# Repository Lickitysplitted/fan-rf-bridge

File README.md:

# Fan RF Bridge

Control RF-remote ceiling fans from Home Assistant, with two-way tracking: the
bridge transmits fan commands and also listens to the handheld remotes, so HA
stays in sync when someone uses the remote.

Hardware: a [wESP32](https://wesp32.com/) (PoE ESP32) running ESPHome, plus a
custom HAT carrying 433 MHz and 315 MHz ASK transmitters (NiceRF STX882) and
receivers (NiceRF SRX882S).

Fans are just what I built it for. The bridge can send and listen to most
fixed-code 433.92 MHz and 315 MHz OOK remotes: lights and plug-in outlets,
blinds and shades, fireplaces, doorbells, and wireless door/motion sensors
(receive only). The same capture → transmit script → template entity pattern
applies; see [Adding devices](#adding-devices). Rolling-code devices (garage
doors, car fobs, gates) and FSK remotes won't work.

> **This is a reference build, not a drop-in config.** Every remote ID and
> code in this repo belongs to my remotes, and the entity names match my
> five fans. Flashed as-is, it will control nothing of yours. Capture your own
> remotes and replace the codes first; see
> [Using it with your own fans](#using-it-with-your-own-fans) and
> [Adding devices](#adding-devices). Other fan models need their own decoding.

Supported fans (one transmitter per band drives every fan of that model; each
remote has its own ID):

| Model | Remote FCC ID | Band | Encoding | HA entities |
|---|---|---|---|---|
| A | 2ABUP-FT0317A | 433.92 MHz | 40-bit PWM: 24-bit remote ID + cmd byte ×2 | 6-speed fan + reverse button |
| B (Harbor Breeze) | A25-FA0188A | 315 MHz | Manchester OOK, replayed raw | 3-speed fan + light |

## Repo layout

| Path | What |
|---|---|
| `fan-control.yaml` | ESPHome config: TX scripts, RX decoders, fan/light entities |
| `fanb_codes.h` | Fan B raw pulse tables (TX) and the RX matcher |
| `secrets.example.yaml` | Template for `secrets.yaml` |
| `fanA-433.txt`, `fanA2-433.txt`, `fanB*-315.txt` | rtl_433 captures the codes were decoded from |
| `fanB_timings.json` | Fan B pulse trains extracted from the captures |
| `make_fana_iq.py`, `make_fanb_iq.py` | Generate HackRF IQ files to replay a command (used to verify codes before the hardware existed) |
| `fan A/B button presses.txt` | Order of button presses in the captures |
| `pcb/` | KiCad 10 project for the HAT, generated by `pcb/make_board.py`; Gerbers in `pcb/fan-hat-gerbers.zip`. See `pcb/README.md` |
| `case/` | 3D-printable case (tall base + magnetic lid). See `case/README.md` |

## Using it with your own fans

The remote IDs in `fan-control.yaml` and `fanb_codes.h` are for **my** remotes.
Even fans of the same models need changes: each remote has its own ID. Rename
or remove fan entities to match how many fans you have. To use your own:

1. Capture each remote (see [Capturing a remote](#capturing-a-remote)), or with an RTL-SDR and
   [rtl_433](https://github.com/merbanan/rtl_433) (`rtl_433 -f 433.92M -A` /
   `-f 315M -A`; 315 MHz needed low gain, `-g 9.9`).
2. Fan A: the 24-bit remote ID is the first 3 bytes of each frame; replace the
   `prefix:` strings and the `rid ==` checks in the RX lambda.
3. Fan B: replace the pulse tables in `fanb_codes.h` (decoded from the
   triq.org links rtl_433 prints).

Other remotes need their own decode, but the TX script / RX lambda / echo
suppression pattern carries over.

## Building the firmware

Replace the remote codes with your own first (see above). The capture step
below can run on the bridge before any codes are in.

```sh
pip install esphome
cp secrets.example.yaml secrets.yaml        # then fill in a key
esphome run fan-control.yaml                # first flash over USB/serial
esphome run fan-control.yaml --device <ip>  # later updates over the network
```

The wESP32's V+ defaults to 12 V; **bridge its 5 V jumper** before fitting the
radios.

## Adding devices

### Capturing a remote

The bridge can capture by itself. Temporarily add `dump:` to the receiver for
the band, flash, and watch the log while pressing each button a few times:

```yaml
remote_receiver:
  - id: rx433            # or rx315
    ...
    dump: all            # tries ESPHome's built-in decoders, then prints raw
```

```sh
esphome run fan-control.yaml --device fan-rf-bridge.local
esphome logs fan-control.yaml --device fan-rf-bridge.local > capture.txt
```

- If a built-in decoder (`rc_switch`, `nexa`, ...) recognises it, the log
  prints a ready-made transmit action. Use that and skip the raw tables.
- Otherwise you get `Received Raw:` lines: microsecond durations, positive =
  carrier on, negative = off. Each button repeats the same burst; diff the
  buttons to find the ID and command bits.
- The SRX882 stretches marks by up to ~150 µs on strong signals, so match on
  short/long rather than exact times (`fanb_match` does this).
- Remove `dump:` when done; it floods the log.

rtl_433 with an RTL-SDR does the same from a PC and auto-decodes many
protocols: `rtl_433 -f 433.92M -A` or `-f 315M -g 9.9 -A`. The original codes
in this repo came from those captures (`fanA-433.txt`, `fanB*-315.txt`).

Only 433.92 and 315 MHz OOK/ASK devices work with this hardware. FSK remotes,
other bands, and rolling-code devices (garage doors, cars) won't.

### Another fan of an existing model

**Model A** (needs its 24-bit remote ID, the first 3 bytes of a frame):

1. Copy the `Fan A1` block under `fan:`. Rename everything `a1` in it (`name`,
   `id`, the `&a1_speed` anchor and its `*a1_speed` alias, `id(fan_a1)` in the
   speed lambda), and put the new remote's ID as a 24-bit binary `prefix:` in
   both `script.execute` calls.
2. Copy a `Fan A1 Reverse` button with the same prefix.
3. In the `rx433` lambda, add the ID to the lookup:
   `rid == 0x00CE17 ? id(fan_a1) : rid == 0x114017 ? id(fan_a2) : rid == 0xNNNNNN ? id(fan_a3) : nullptr`.

**Model B** (replayed raw, so the pulse tables are needed):

1. In `fanb_codes.h`, grow `FANB[3][5]` to `FANB[4][5]` and add a row with the
   five raw trains (speed1, speed2, speed3, off, light), in that order.
   Different remote revisions use different command bytes (see the B3
   comment), so capture every button.
2. In `fanb_match` (same file), change `f < 3` to `f < 4`.
3. Copy the `Fan B3` block under `fan:`, rename `b3` → `b4` throughout
   (including `id(fan_b3)` in the speed lambda), and use `fan: 3` in its
   script calls.
4. Copy a Fan B light: the `out_light_b3` template output (with `fan: 3`)
   and its `light: binary` entry pointing at the new output.
5. In the `rx315` lambda, extend the two `fi == ...` chains to include the new
   fan and light.

### A different kind of device

Follow the same pattern as the fans:

1. **Capture and decode** (above). Note whether a command is absolute
   (e.g. "speed 2") or a toggle (e.g. "power"). Toggles can get out of step with
   HA, as with Fan A power.
2. **Transmit.** Add a script modelled on `fanb_send`. Use a built-in action
   if `dump: all` found one, otherwise `transmit_raw` with the timings.
   Real remotes repeat a frame 5–10 times, so do the same. Keep the script's
   two guards: skip sending while `from_rx` is set (so an RX state update
   doesn't retransmit) and set `last_tx` (so the bridge ignores hearing
   itself).
3. **Entities.** Pick a fitting `template` type (fan, light via a template
   output, switch, button) and call the script from its actions.
4. **Receive (optional).** Add a branch to the band's `on_raw` lambda that
   matches the frames, ignores repeats within 1 s, and publishes the new
   state with `from_rx` set.

Before the firmware existed, codes were first checked by replaying them with a
HackRF (`make_fana_iq.py` / `make_fanb_iq.py` → `hackrf_transfer -t`). You can
skip that step and test straight from the bridge.

## Operating it

**Adding to Home Assistant.** Plug the bridge into a PoE port. HA discovers it
under Settings → Devices & services as "Fan RF Bridge"; click Configure and
paste `api_encryption_key` from `secrets.yaml`. Give it a DHCP reservation so
OTA updates keep finding it (`fan-rf-bridge.local` also works).

**Entities.**

| Entity | What it does |
|---|---|
| Fan A1, Fan A2 | On/off and 6 speeds |
| Fan A1 Reverse, Fan A2 Reverse (buttons) | Flip the direction (summer/winter) |
| Fan B1, Fan B2, Fan B3 | On/off and 3 speeds |
| Fan B1 Light … Fan B3 Light | Fan light on/off |
| Status LED | The LED on the HAT (turn off if it bothers you) |

Use them like any HA fan or light: dashboard cards, voice assistants,
automations, scenes.

**Using the handheld remotes.** Keep using them. The bridge hears every press,
so HA updates to match within a second.

**State can drift.** The fans don't report back, so HA only knows what it
sent or heard. If a press is missed (remote out of range, bridge rebooting,
fan switched at the wall), HA shows the wrong state. To fix it, set the fan or
light in HA to what it really is, then press the button once more:

- Fan A power is a toggle. If HA says off while the fan is spinning, turn it
  "on" in HA (no change on the fan), then off.
- Fan B lights are a toggle too. Same fix: flip the HA light once to match,
  then use it normally.
- Fan B speeds and off are absolute, so they can't drift. Picking a speed
  always lands on that speed.

After a reboot or power loss everything shows off in HA, whatever the fans are
actually doing.

**Status LED.** Steady on = running normally. Slow blink = warning (e.g. HA not
connected yet). Fast blink = error.

**Updating firmware.** `esphome run fan-control.yaml --device fan-rf-bridge.local`.
It needs `ota_password` from `secrets.yaml`.

## Notes

- RF is one-way per command; fan state in HA is assumed, corrected by RX when a
  remote is used. Fan A power is a toggle code; Fan B light is a toggle.
- The bridge hears its own transmissions, so RX is ignored for 2 s after TX.
- Datasheets: wESP32 product brief (silicognition.com), NiceRF STX882 / SRX882
  (nicerf.com).

## License

MIT (see `LICENSE`), except `case/`, which is CC BY-NC-SA as a remix of
notjj's wESP32 case (see `case/README.md`).

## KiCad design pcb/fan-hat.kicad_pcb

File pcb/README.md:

# wESP32 RF hat (fan-hat)

75 × 40 mm board that stacks on top of the wESP32 on its four mounting holes and
plugs into JP1. Carries the two STX882 transmitters and two SRX882 receivers in
sockets, the 5 V → 3.3 V dividers for the receiver data lines, decoupling and a
status LED. Replaces the Perma-Proto + Adafruit 757.

Open `fan-hat.kicad_pro` in KiCad 10. `make_board.py` regenerates everything
(schematic, placed AND routed PCB with filled GND pours, custom footprint/symbol)
and checks that schematic nets == PCB pad nets, ERC and DRC (all clean):

    & "$env:LOCALAPPDATA\Programs\KiCad\10.0\bin\python.exe" make_board.py

Edit positions/nets/tracks in the script (`PARTS`, `TRACKS`), not in KiCad —
re-running overwrites the files. `fan-hat-gerbers.zip` is the fab upload
(2-layer, 1.6 mm, any finish; JLCPCB/PCBWay 5 pcs).

## Geometry (from the product brief)

- Holes ⌀3.2 at 3.5 mm from each edge (wESP32: ⌀3, same spots), M2.5 hardware.
- JP1 pin 1 = OUTER column (1.8 mm from the right edge), 5.0 mm up from the
  bottom-right (non-plated) hole, header centred on the 40 mm axis; pin 2
  inboard, pin 3 above pin 1. **Caliper-check on the real board:** pin 1 at
  1.8 mm from the right edge, 8.6 mm from the bottom edge.
- Left 22 mm of the underside is kept empty: RJ45 (15.2 mm tall) and 12 mm
  electrolytics are there. Right end underside is the 2×10.
- SRX882: pins 2 and 6 are both GND, pins 1 and 7 both ANT (NiceRF datasheet,
  RFLink wiring page), so the socket is a plain 1×4 on pins 3–6 (VCC, CS, DATA,
  GND). Pins 1–2 hang free above the board (measured pin 2 → 3 gap 18.22 mm is
  drawn on silk only). Coil solders to pin 1 or the pin-7 hole.
- Modules lie FLAT in their sockets (pins straight, not bent): the pin row is
  1.2 mm (SRX) / 1.8 mm (STX) from one long edge and the body lies over the
  board. The unit mounts on the wall with the RJ45 end DOWN, so "up" is the
  JP1 end (+x): the two SRX882 lie along the board with pin 1 (ANT end) toward
  +x, the two STX882 sit at the top with their bodies overhanging the JP1 pads
  (they are 8.5 mm up on their sockets — pads and screw heads are below them).
  All four ANT holes (silk circles) face +x, so the coils exit past the top edge.
  STX882 ANT pad is at the DATA end of the socket (confirmed from the module).

## Stack

Hat underside is 18 mm above the wESP32 top (M2.5 × 18 mm standoffs ×4).
JP1 ships as bare pads. Used: 3M 929836-04-10 2x10 header soldered into
JP1 UPSIDE DOWN (short 6 mm side in the board, 12.95 mm side pointing up; trim
the stubs underneath), mating a plain 2x10 female socket (8.5 mm body) on the
hat's underside. Socket opening sits ~9.5 mm above the wESP32, the pin tips at
~15.5 mm, so ~6 mm insertion. Ordinary 6 mm-pin headers won't reach.
Fallback: two Arduino-style stackable female headers plugged into each other
on JP1 and a plain male header on the hat - same footprint.

Above the hat: modules lie flat on 8.5 mm sockets, so ≈ 10–14 mm total; the
coil antennas solder to the ANT hole on each module and extend past the top
edge — the hat has no antenna pads.

## BOM

| Ref | Part | Qty |
|---|---|---|
| J1 | 2×10 female socket (hat) + 2×10 long-pin male header (wESP32 JP1) | 1 + 1 |
| U1, U2 | SRX882 (433, 315) on 1×4 female headers | 2 + 2 |
| U3, U4 | STX882 (433, 315) on 1×3 female header | 2 + 2 |
| R1, R3 | 10 kΩ axial | 2 |
| R2, R4 | 20 kΩ axial | 2 |
| R5 | 330 Ω axial | 1 |
| D1 | 3 mm LED | 1 |
| C1–C4 | 100 nF ceramic disc, 2.5 mm | 4 |
| C5 | 10 µF electrolytic, 5 mm ⌀, 2 mm pitch | 1 |
| H1–H4 | M2.5 × 18 mm standoff + screws | 4 |

Routing notes: JP1's odd column is reached through the 0.84 mm gap between the
header columns (IO23 on top, IO5 on the bottom), which boxes in pin 9 — so pin 9
is left NC and GND uses pins 1 and 19. GND is the pours on both sides plus two
short stitches (JP1.1→U4.3, D1.1→C5.2). No vias.

Nets: IO4 → STX-433 DATA, IO5 → STX-315 DATA, SRX-433 DATA → 10k/20k → IO34,
SRX-315 DATA → 10k/20k → IO35, IO23 → 330 Ω → LED. Everything runs on V+ (5 V,
jumper bridged); 3.3 V unused. Receiver CS tied to 5 V.

## Assembly note (case)

The printed case has magnet blocks in the corners at the antenna end that reach
up to 1 mm inside the HAT's long edges (x 69–75; the wESP32 sits 0.6 mm
off-centre in the case). Bend both SRX coils at least 2.5 mm inboard where they
pass that end: SRX-433 to y ≈ 5.5, SRX-315 to y ≈ 36.3. That clears the blocks
in either board orientation with ≥ 0.7 mm margin and passes over the STX
modules. The STX coils are already inboard.

Coil height: the case's antenna slot tops out 37 mm above the case floor, so
every coil must leave its module with its axis no more than 11 mm above the HAT
top. The module PCBs sit at 8.5–9.5 mm (socket + board), so solder each coil
with its lead bent so the coil runs level with the module board (axis ≈ 9.5–10
mm), not perched on top of it.

## Before ordering

1. Open the board in KiCad, run DRC once yourself, eyeball the 3D view.
2. Upload `fan-hat-gerbers.zip`.
3. Firmware already drives the LED (`status_led` light on GPIO23 in `fan-control.yaml`).

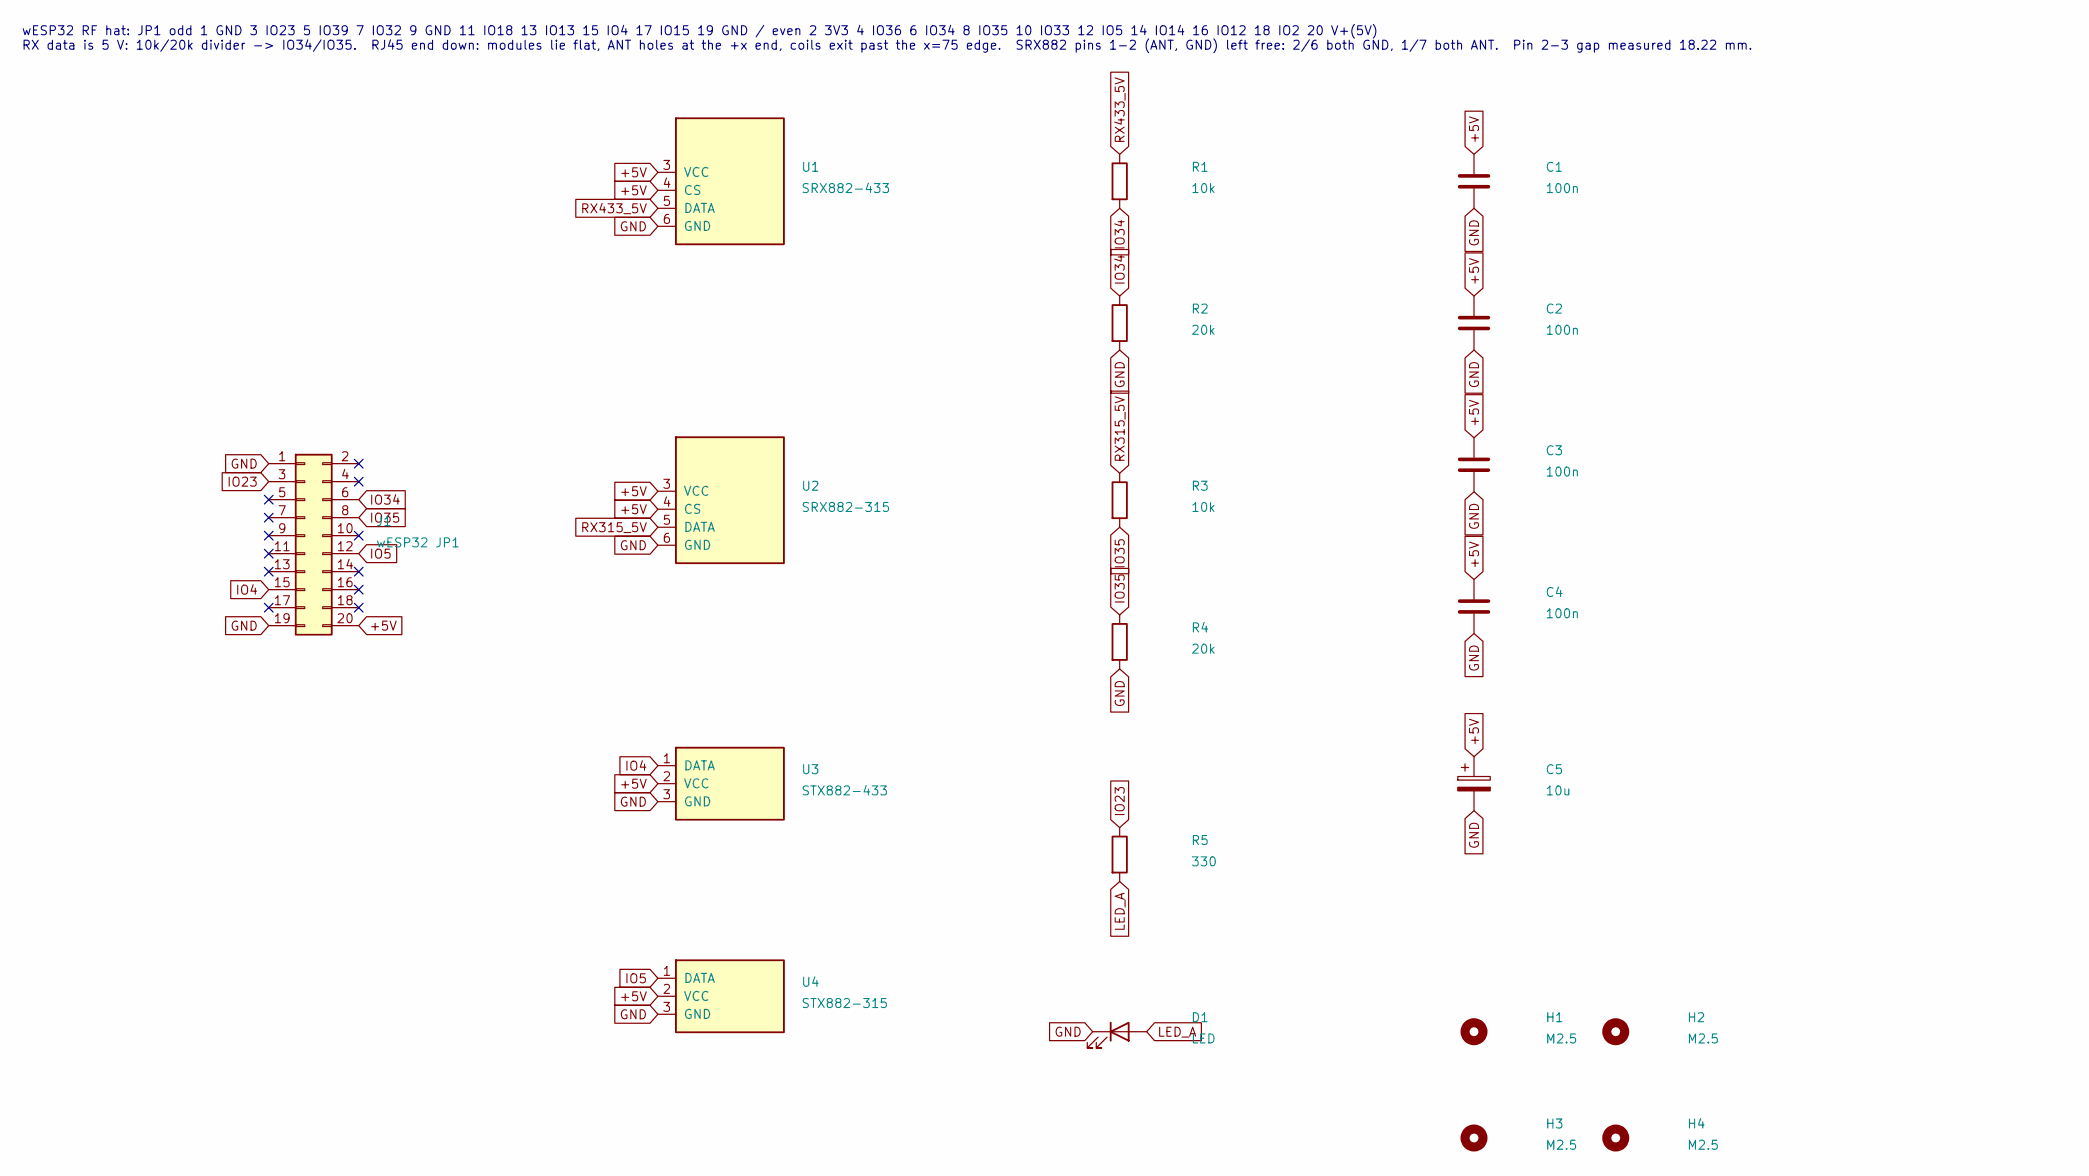
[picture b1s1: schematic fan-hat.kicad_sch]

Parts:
C1, C2, C3, C4: 100n; C_Disc_D5.0mm_W2.5mm_P2.50mm
C5: 10u; CP_Radial_D5.0mm_P2.00mm
D1: LED; LED_D3.0mm
H1, H2, H3, H4: M2.5; MountingHole_3.2mm_M3
J1: wESP32 JP1; PinSocket_2x10_P2.54mm_Vertical
R1, R3: 10k; R_Axial_DIN0207_L6.3mm_D2.5mm_P7.62mm_Horizontal
R2, R4: 20k; R_Axial_DIN0207_L6.3mm_D2.5mm_P7.62mm_Horizontal
R5: 330; R_Axial_DIN0207_L6.3mm_D2.5mm_P7.62mm_Horizontal
U1: SRX882-433; SRX882_Socket
U2: SRX882-315; SRX882_Socket_BodyDown
U3: STX882-433; PinSocket_1x03_P2.54mm_Vertical
U4: STX882-315; PinSocket_1x03_P2.54mm_Vertical

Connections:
+5V: C1.1, C2.1, C3.1, C4.1, C5.1, J1.20, U1.3 (VCC), U1.4 (CS), U2.3 (VCC), U2.4 (CS), U3.2 (VCC), U4.2 (VCC)
GND: C1.2, C2.2, C3.2, C4.2, C5.2, D1.1 (K), J1.1, J1.19, R2.2, R4.2, U1.6 (GND), U2.6 (GND), U3.3 (GND), U4.3 (GND)
IO4: J1.15, U3.1 (DATA)
IO5: J1.12, U4.1 (DATA)
IO23: J1.3, R5.1
IO34: J1.6, R1.2, R2.1
IO35: J1.8, R3.2, R4.1
LED_A: D1.2 (A), R5.2
RX315_5V: R3.1, U2.5 (DATA)
RX433_5V: R1.1, U1.5 (DATA)

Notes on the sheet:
wESP32 RF hat: JP1 odd 1 GND 3 IO23 5 IO39 7 IO32 9 GND 11 IO18 13 IO13 15 IO4 17 IO15 19 GND / even 2 3V3 4 IO36 6 IO34 8 IO35 10 IO33 12 IO5 14 IO14 16 IO12 18 IO2 20 V+(5V) RX data is 5 V: 10k/20k divider -> IO34/IO35. RJ45 end down: modules lie flat, ANT holes at the +x end, coils exit past the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

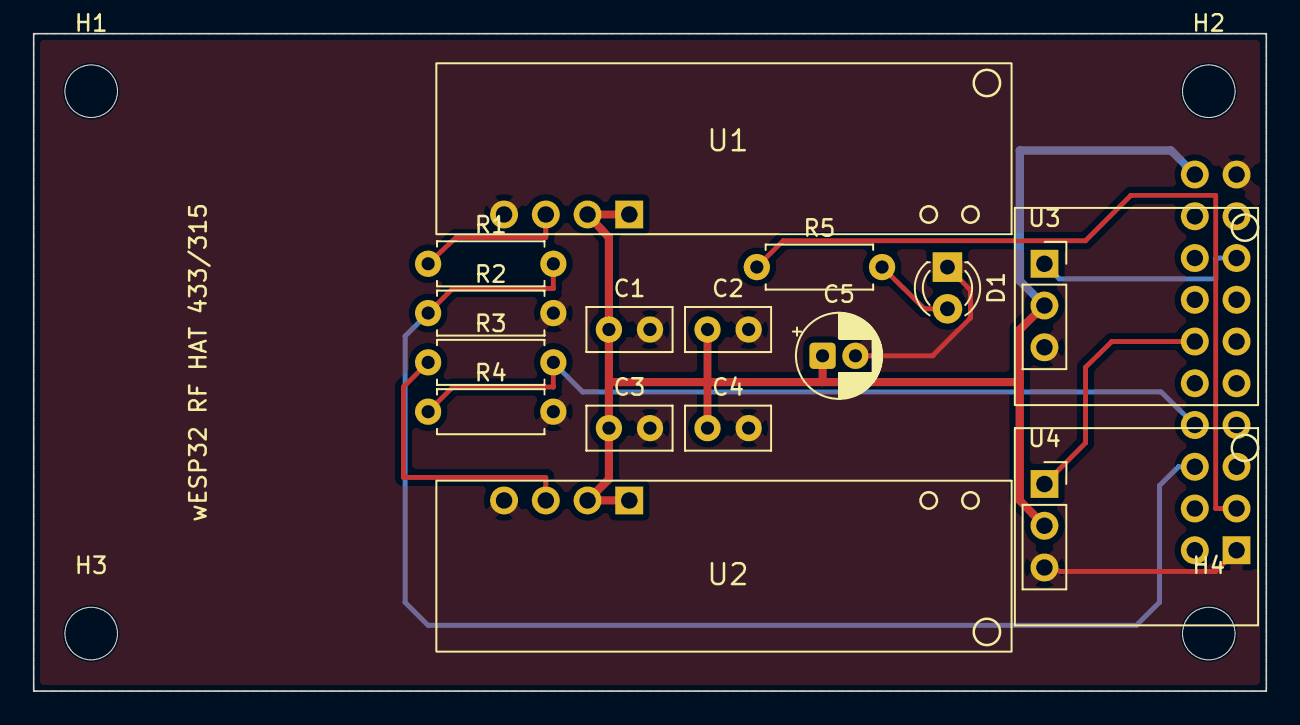
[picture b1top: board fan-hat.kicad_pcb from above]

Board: 2 copper layers, 75.0 x 40.0 mm, 20 parts (1 on the bottom side), 10 nets.
